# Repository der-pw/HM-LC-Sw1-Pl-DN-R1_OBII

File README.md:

# HM-LC-Sw1-Pl-DN-R1_OBII      

### Dieses Projekt beschreibt den Umbau eines WLAN-Schaltaktors ([der in den OBI-Baumärkten verkauft wird](https://www.obi.de/hausfunksteuerung/wifi-stecker-schuko-weiss/p/4077806)) zum HM-LC-Sw1-Pl-DN-R1_OBII 
... und basiert auf der hervorragenden Arbeit von [pa-pa](https://github.com/pa-pa/AskSinPP), [Jérôme](https://github.com/jp112sdl/Beispiel_AskSinPP), sowie [stan23](https://github.com/stan23), der mit seinem Umbau OBI-Wifi-Stecker zu [HM-LC-Sw1-Pl-DN-R1_OBI](https://github.com/stan23/HM-LC-Sw1-Pl-DN-R1_OBI) der ersten Version, gezeigt hat wie es geht.

Weitere Informationen gibt es im [Wiki](https://github.com/der-pw/HM-LC-Sw1-Pl-DN-R1_OBII/wiki).

Dieses Werk ist lizenziert unter einer [Creative Commons Namensnennung - Nicht-kommerziell - Weitergabe unter gleichen Bedingungen 4.0 International Lizenz](http://creativecommons.org/licenses/by-nc-sa/4.0/).

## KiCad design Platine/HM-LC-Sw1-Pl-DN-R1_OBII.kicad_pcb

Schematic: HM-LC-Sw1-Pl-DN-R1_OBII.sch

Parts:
C1, C2, C3: 100n; C_0603_1608Metric_Pad1.05x0.95mm_HandSolder
J3: Conn_01x01_Female; PinHeader_1x01_P2.00mm_Vertical
R1: 10k; R_0603_1608Metric_Pad1.05x0.95mm_HandSolder
U1: ATmega328P-AU; TQFP-32_7x7mm_P0.8mm
U2: CC1101
U3: WROOM-02-DUKOS; ESP-WROOM-02-Dukos

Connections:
/BUTTON-1: U1.11 (PD7), U3.14
/CONFIG: U1.12 (PB0), U3.15
/LED-G: U1.2 (PD4), U3.4
/RELAY: U1.1 (PD3), U3.5, U3.10
GND: C1.2, C2.2, C3.2, U1.3 (GND), U1.5 (GND), U1.21 (GND), U2.2, U3.9, U3.13, U3.18
unnamed: J3.1, R1.2, U1.29 (~RESET~/PC6)
unnamed: U1.14 (PB2), U2.8
unnamed: U1.15 (PB3), U2.3
unnamed: U1.16 (PB4), U2.5
unnamed: U1.17 (PB5), U2.4
unnamed: U1.32 (PD2), U2.7
VCC: C1.1, C2.1, C3.1, R1.1, U1.4 (VCC), U1.6 (VCC), U1.18 (AVCC), U1.20 (AREF), U2.1, U3.1

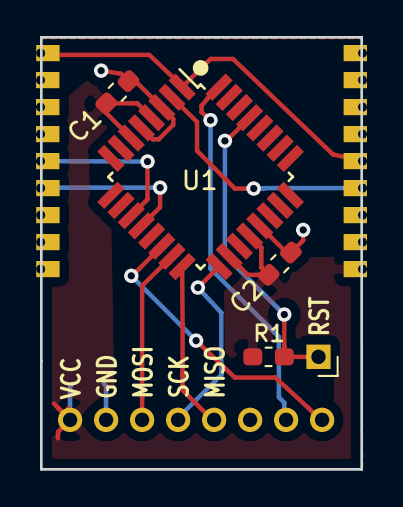
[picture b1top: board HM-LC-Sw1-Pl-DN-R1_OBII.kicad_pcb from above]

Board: 2 copper layers, 17.8 x 24.0 mm, 8 parts (1 on the bottom side), 12 nets.

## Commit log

2019-02-03 upload
2020-01-27 some Tests for PCB Panelizer

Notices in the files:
README.md:
License: CC BY-NC-SA 4.0
Creative Commons Lizenzvertrag
